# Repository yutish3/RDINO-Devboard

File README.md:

# Rdino - 2040
rp-2040 development board in the shape of arduino uno r3 so it supports its hats and also has esp32 for wifi and bluetooth and 5x5 grid of neo pixel leds

Journal 1	:- 2.0 hours

Journal 2	:- 1.5 hours

Journal 3	:- 0.4 hours

Journal 4	:- 1.5 hours

Journal 5	:- 1.0 hours

Journal 6	:- 1.5 hours

Journal 7	:- 1.3 hours

Journal 8	:- 2.0 hours

Journal 9	:- 1.0 hours

Journal 10	:- 0.5 hours

Journal 11	:- 2.0 hours

Journal 12	:- 2.5 hours

Journal 13	:- 2.0 hours

Journal 14	:- 5.2 hours

Journal 15	:- 1.0 hours

Journal 16	:- 0.5 hours

Journal 17	:- 0.5 hours

Journal 18	:- 5.5 hours

Journal 19	:- 2.0 hours

Journal 20	:- 3.0 hours

## VISION
main goals I had was making it is that I wanted to have a powerful board on which Arduino hats can fit with wireless capabilities so I used both rp 2040 and esp 32 and connected gpios of both so rp 2040 can off load some tasks to esp 32. so in a sense it is like Arduino UNO but on steroids 

and for usage too it can be used like a normal Arduino UNO 

it has dual microcontroller so all the less important repetative tasks can be off loaded to esp32 and main work can be done by the rp 2040 chip with extra 16M bit memory
and it can be used foor any project like lfr robot , micromouse , rc car etc

## what makes it special (main components)
&#9679; RP2040 :- main microcontroller

&#9679; W25Q128JVS :- 128Mbit Flash Memory for extra juice

&#9679; ESP32-C3-WROOM-02 :- backup microcontroller with wifi and Bluetooth capabilities 

&#9679; 25 X WS2812B-2020 :- programmable rgb leds

## Images

| Component | Purpose | Qty | Cost (INR) | Distributor |
| --- | --- | --- | --- | --- |
| RP2040 (QFN-56) | Main Microcontroller | 1 | ₹81.00 | [Evelta](https://evelta.com/rp2040-264kb-sram-dual-arm-cortex-m0-processor-mcu-by-raspberry-pi/?srsltid=AfmBOopaIG6fpnSNGs3z4S0e6P0bgP9_VYOyHm1yW1iu5uU8jt_uu5J_) |
| ESP32-C3-WROOM-02 | Wi-Fi / BLE Module | 1 | ₹312 | [Evelta](https://evelta.com/esp32-c3-wroom-02-n4-wi-fi-ble-module-4mb-flash-pcb-antenna/?sku=136-ESP32-C3-WROOM-02-N4&utm_source=google&utm_campaign=19958243666&utm_medium=cpc&utm_content=&utm_term=&gad_source=1&gad_campaignid=19958265965&gclid=Cj0KCQjwsMLSBhD9ARIsAIpUTDqEPgMN1OtKYFDDmMqUSGKSXAjHzA4DRwzgzZp3zSiW1o8-RgKeGbgaAoSMEALw_wcB) |
| W25Q128JVS (SOIC-8) | 128Mbit Flash Memory | 1 | ₹223 | [Evelta](https://evelta.com/serial-nor-flash-memory-128mbit-8pin-soic/?sku=153-W25Q128JVSIQ&utm_source=google&utm_campaign=19958243666&utm_medium=cpc&utm_content=&utm_term=&gad_source=1&gad_campaignid=19958265965&gclid=Cj0KCQjwsMLSBhD9ARIsAIpUTDqgAe2PFV_ZbwzCVTig-jSF6n-lNv5TzVO5kI0fkOoLNDz-UcC87KoaAvCyEALw_wcB) |
| AP2112K-3.3 (SOT-23-5) | 3.3V LDO Voltage Regulator | 1 | ₹24 | [Evelta](https://evelta.com/linear-voltage-regulator-positive-fixed-1-output-300ma-ic-sot-23-5/?sku=035-TLV74033PDBVR&utm_source=google&utm_campaign=19958243666&utm_medium=cpc&utm_content=&utm_term=&gad_source=1&gad_campaignid=19958265965&gclid=Cj0KCQjwsMLSBhD9ARIsAIpUTDpVNRkkdR8DkeeqQDI-B0SV4mmE5r7KHuDlczT8pWqQnIAxcDNvTTQaAnOdEALw_wcB#productDescription) |
| WS2812B-2020 (PLCC4) | Addressable RGB LEDs (D1-D24, D27, D29, D31) | 25 | ₹275 | [Robu](https://robu.in/product/1-month-warranty-953/?gad_source=1&gad_campaignid=17427802703&gclid=Cj0KCQjwsMLSBhD9ARIsAIpUTDpt1pzF430Rd8rggMbqOhyDVxqaDctheh1CFh1cCbUzKa_cTqI4nuYaAhGvEALw_wcB) |
| 74AHCT125 | 3.3v to 5v converter | 1 | ₹113 | [Lioncircuit](https://www.lioncircuits.com/parts/74AHCT125PW%2C118) |
| Standard LED (0603) | Status Indicator (D26) | 1 | ₹3.3 | [evelta](https://evelta.com/0603-orange-chip-led/?srsltid=AfmBOopJK48IT0WFYCzFETDcCPIIkiPRop17X2j5vajIVfQTBZ31vxPa) |
| USB-C Receptacle 14-Pin | Power and Data Interface (J1) | 1 | ₹8 | [Hubtronics](https://hubtronics.in/usb-type-c-16p-female-connector-surface-mount?srsltid=AfmBOordf7MpBH0Qx-t9NQyY5B-fdjtzOuCBNZ2MHx8Cz8tkCzKM3Jp4zG4) |
| 1x04 Pin Header/Socket | I/O Expansion / Programming (J6) | 1 | ₹11 | [Robu](https://robu.in/product/fh2-0-09-04pzd-xunpu-plugin1x4-pin-2mm-female-headers-rohs/?gad_source=1&gad_campaignid=17427802703&gclid=CjwKCAjw08fSBhA7EiwAfbQTsMGuGFKjKxeAs85tsGpJZ_VgBg9C0syUiuKSdEVnRGq6vaZT8pyhIhoCEKcQAvD_BwE)|
| 1x06 Pin Header/Socket | I/O Expansion (J2) | 5 | ₹53 | [Robu](https://robu.in/product/6-pin-female-11mm-tall-stackable-header-connector-for-arduino-5pcs/) |
| 1x08 Pin Header/Socket | I/O Expansion (J4, J5) | 2 | ₹32 | [Robu](https://robu.in/product/fh1-27-01-08pzd-xunpu-plugin1x8-pin-1-27mm-female-headers-rohs/?gad_source=1&gad_campaignid=17427802703&gclid=CjwKCAjw08fSBhA7EiwAfbQTsAXYrqE1Rld57TzQKy9yslqVRvfkEbmGVCeCCZim9T4gCUaC_6xX4xoCpCAQAvD_BwE) |
| 1x10 Pin Header/Socket | I/O Expansion (J3) | 1 | ₹17 | [Robu](https://robu.in/product/fh1-27-01-10pzd-xunpu-plugin1x10-pin-1-27mm-female-headers-rohs/) |
| Push Button (KMR2) | Reset / User Input (SW1, SW2) | 2 | ₹126 | [Robu](https://robu.in/product/kmr221nglfs-ck-2-8mm-0-5mm-round-button-50ma-vertical-welding-4-2mm-spst-2n-32v-smd-tactile-switches-rohs/) |
| 1.1kΩ Resistor (0603) | Current Limiting / Pull-up | 1 | ₹1 | [Robu](https://robu.in/product/0603waj0112t5e-uniohm-royal-ohm-100mw-thick-film-resistors-75v-%C2%B1100ppm-%E2%84%83%C2%B15-1-1k%CF%89-0603-chip-resistor-surface-mount-rohs/) |
| 4.7kΩ Resistor (0603) | I2C / General Pull-up | 2 | ₹5 | [Robu](https://robu.in/product/rt0603brd074k7l-yageo-res-thin-film-0603-4-7k-ohm-0-1-0-1w1-10w-%C2%B125ppm-c-pad-smd-t-r/) |
| 10kΩ Resistor (0603) | Pull-up / Pull-down | 3 | ₹3 | [Robu](https://robu.in/product/10k-ohm-1-4w-0603-surface-mount-chip-resistor-pack-of-100/) |
| 5.1kΩ Resistor (0603) | USB-C CC line Pull-down | 2 | ₹3 | [Robu](https://robu.in/product/rt0603fre075k1l-yageo-100mw-thin-film-resistor-75v-%C2%B150ppm-%E2%84%83-%C2%B11-5-1k%CF%89-0603-chip-resistor-surface-mount-rohs/) |
| 1μF Capacitor (0603) | Decoupling / Bypass | 6 | ₹8.5 | [Robu](https://robu.in/product/1uf-1000nf-50v-capacitor-0603-smd-package-pack-of-20/) |
| 10pF Capacitor (0603) | Crystal Load Capacitors | 2 | ₹1 | [Robu](https://robu.in/product/10pf-0603-surface-mount-multilayer-ceramic-capacitor-pack-of-50/) |
| Crystal 3225 (4-Pin) | Clock Source for RP2040 (Y1) | 1 | ₹101 | [lion circuit](https://www.lioncircuits.com/parts/NX3225SA-12MHZ-STD-CSR-6) |
| PCB | PCB | 1 | ₹3375 | [Robu] |
| Hot plate | soldering | 1 | ₹2,749 | [Amazon](https://www.amazon.in/Preheating-Soldering-Preheater-Platform-56x56x35mm/dp/B0C7W3W8C4?source=ps-sl-shoppingads-lpcontext&psc=1&smid=A2PRL1RFFZO5CK) |
| soldering flux | gooye paste to combine components | 1 | ₹400 | [amazon](https://www.amazon.in/Electron-Soldering-Syringe-No-Clean-Electronics/dp/B0GTMJHBJ4) |

The Bare Components : ₹1,708.80

PCB Fabrication (Robu): ₹3,375.00

Assembly Tools (Amazon): ₹3,262.00

Grand Total: ₹8,345.8

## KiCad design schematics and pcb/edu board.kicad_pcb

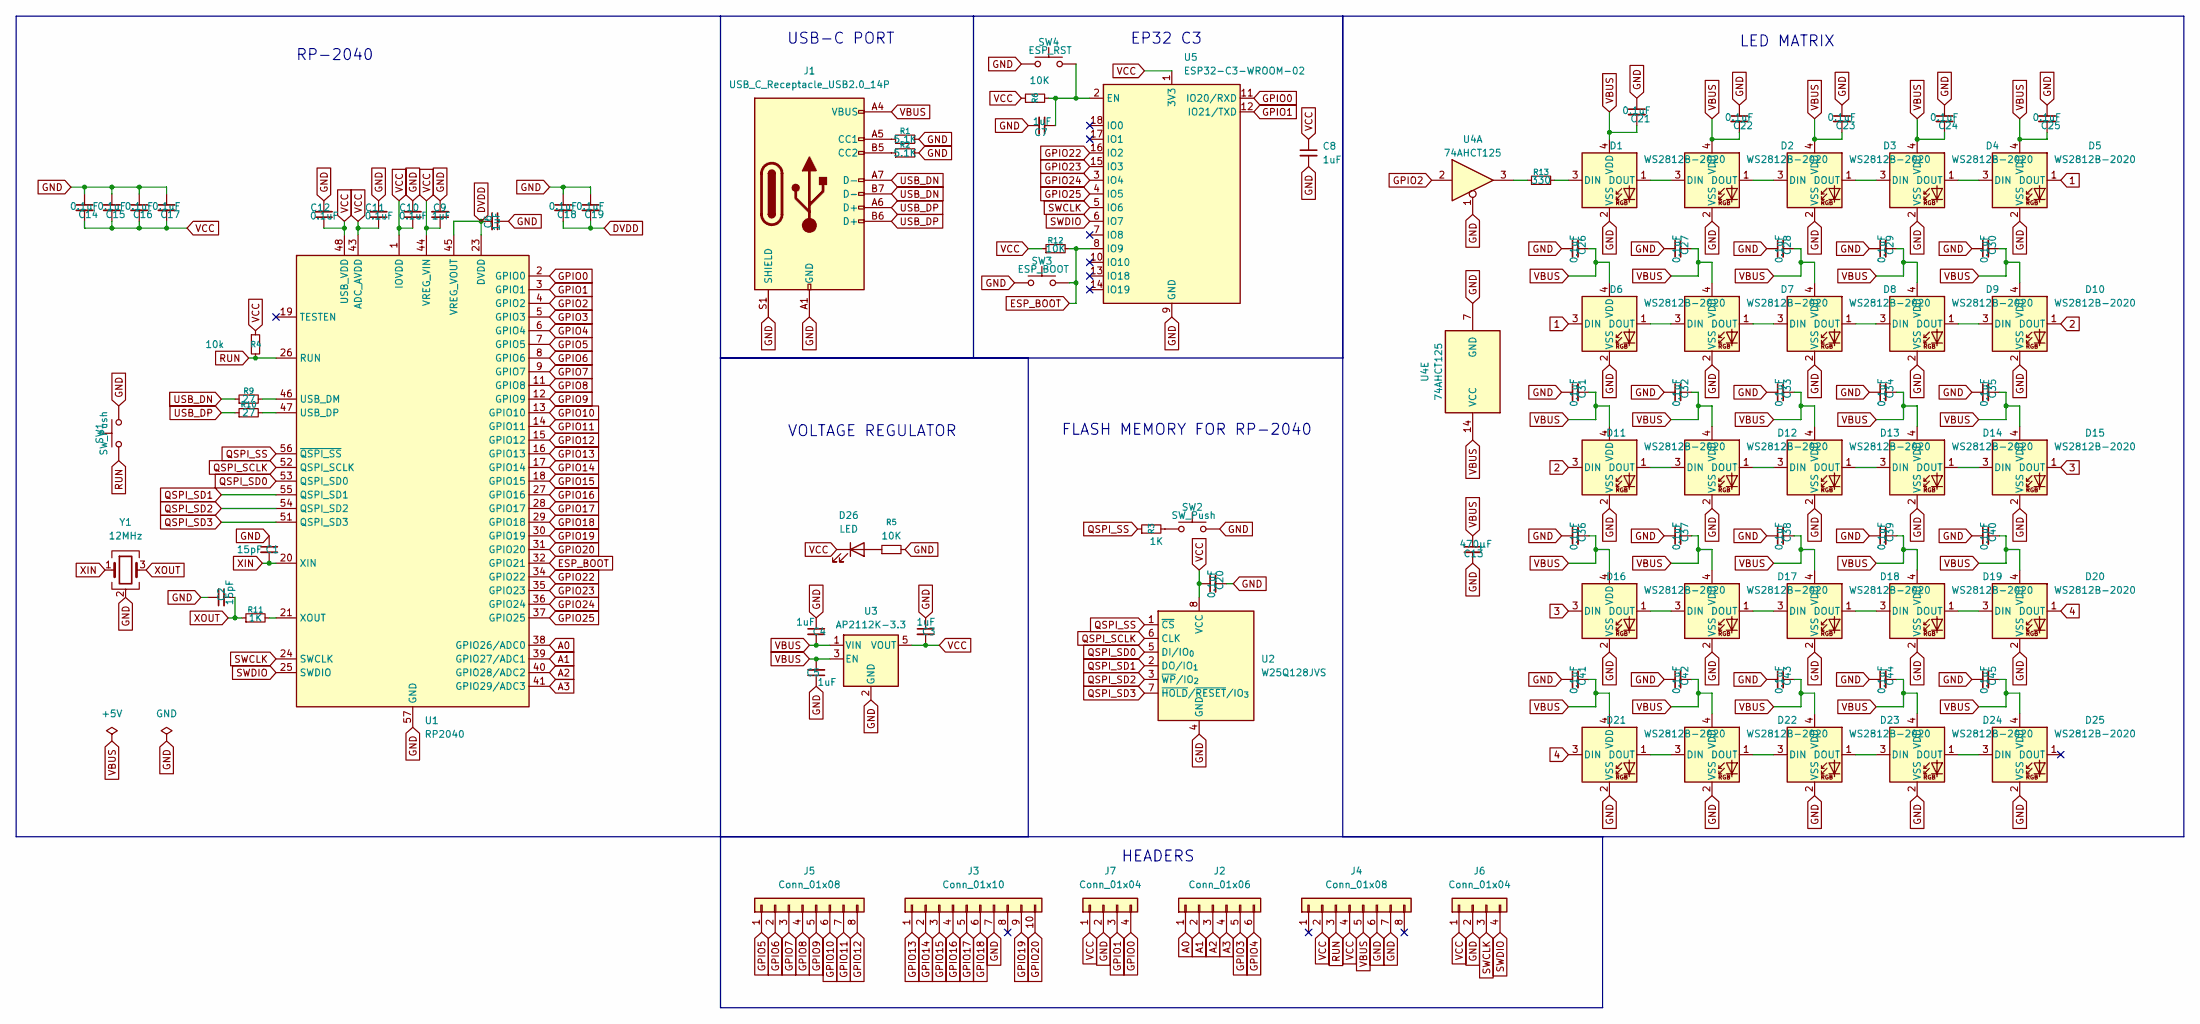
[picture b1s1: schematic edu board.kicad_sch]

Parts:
C1, C2: 15pF; C_0201_0603Metric
C3, C4, C5, C6, C7, C8, C9: 1uF; C_0201_0603Metric
C10, C11, C12, C14, C15, C16, C17, C18, C19, C20, C21, C22, C23, C24, C25, C26, C27, C28, C29, C30, C31, C32, C33, C34, C35, C36, C37, C38, C39, C40, C41, C42, C43, C44, C45: 0.1uF; C_0201_0603Metric
C13: 470μF; C_0201_0603Metric
D1, D2, D3, D4, D5, D6, D7, D8, D9, D10, D11, D12, D13, D14, D15, D16, D17, D18, D19, D20, D21, D22, D23, D24, D25: WS2812B-2020; LED_WS2812B-2020_PLCC4_2.0x2.0mm
D26: LED; LED_0603_1608Metric
J1: USB_C_Receptacle_USB2.0_14P; USB_C_Receptacle_HRO_TYPE-C-31-M-12
J2: Conn_01x06; PinSocket_1x06_P2.54mm_Vertical
J3: Conn_01x10; PinSocket_1x10_P2.54mm_Vertical
J4, J5: Conn_01x08; PinSocket_1x08_P2.54mm_Vertical
J6, J7: Conn_01x04; PinHeader_1x04_P2.54mm_Vertical
R1, R2: 5.1K; R_0201_0603Metric
R3, R11: 1K; R_0201_0603Metric
R4: 10k; R_0201_0603Metric
R5, R6, R12: 10K; R_0201_0603Metric
R9, R10: 27; R_0201_0603Metric
R13: 330; R_0201_0603Metric
SW1, SW2: SW_Push; SW_Push_1P1T_NO_CK_KMR2
SW3: ESP_BOOT; SW_Push_1P1T_NO_CK_KMR2
SW4: ESP_RST; SW_Push_1P1T_NO_CK_KMR2
U1: RP2040; QFN-56-1EP_7x7mm_P0.4mm_EP3.2x3.2mm
U2: W25Q128JVS; SOIC-8_5.3x5.3mm_P1.27mm
U3: AP2112K-3.3; SOT-23-5
U4: 74AHCT125; TSSOP-14_4.4x5mm_P0.65mm
U5: ESP32-C3-WROOM-02
Y1: 12MHz; Crystal_SMD_3225-4Pin_3.2x2.5mm

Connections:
1: D5.1 (DOUT), D6.3 (DIN)
2: D10.1 (DOUT), D11.3 (DIN)
3: D15.1 (DOUT), D16.3 (DIN)
4: D20.1 (DOUT), D21.3 (DIN)
A0: J2.1, U1.38 (GPIO26/ADC0)
A1: J2.2, U1.39 (GPIO27/ADC1)
A2: J2.3, U1.40 (GPIO28/ADC2)
A3: J2.4, U1.41 (GPIO29/ADC3)
DVDD: C6.2, C18.2, C19.2, U1.23 (DVDD), U1.45 (VREG_VOUT), U1.50 (DVDD)
ESP_BOOT: R12.2, SW3.2, U1.32 (GPIO21), U5.8 (IO9)
GND: C1.1, C2.1, C3.1, C4.1, C5.1, C6.1, C7.2, C8.2, C9.2, C10.2, C11.2, C12.2, C13.2, C14.1, C15.1, C16.1, C17.1, C18.1, C19.1, C20.2, C21.1, C22.1, C23.1, C24.1, C25.1, C26.1, C27.1, C28.1, C29.1, C30.1, C31.1, C32.1, C33.1, C34.1, C35.1, C36.1, C37.1, C38.1, C39.1, C40.1, C41.1, C42.1, C43.1, C44.1, C45.1, D1.2 (VSS), D2.2 (VSS), D3.2 (VSS), D4.2 (VSS), D5.2 (VSS), D6.2 (VSS), D7.2 (VSS), D8.2 (VSS), D9.2 (VSS), D10.2 (VSS), D11.2 (VSS), D12.2 (VSS), D13.2 (VSS), D14.2 (VSS), D15.2 (VSS), D16.2 (VSS), D17.2 (VSS), D18.2 (VSS), D19.2 (VSS), D20.2 (VSS), D21.2 (VSS), D22.2 (VSS), D23.2 (VSS), D24.2 (VSS), D25.2 (VSS), J1.A1 (GND), J1.A12 (GND), J1.B1 (GND), J1.B12 (GND), J1.S1 (SHIELD), J3.7, J4.6, J4.7, J6.2, J7.2, R1.2, R2.2, R5.2, SW1.2, SW2.2, SW3.1, SW4.1, U1.57 (GND), U2.4 (GND), U3.2 (GND), U4.1, U4.7 (GND), U5.9 (GND), U5.19 (GND), Y1.2 (G), Y1.4 (G)
GPIO0: J7.4, U1.2 (GPIO0), U5.11 (IO20/RXD)
GPIO1: J7.3, U1.3 (GPIO1), U5.12 (IO21/TXD)
GPIO2: U1.4 (GPIO2), U4.2
GPIO3: J2.5, U1.5 (GPIO3)
GPIO4: J2.6, U1.6 (GPIO4)
GPIO5: J5.1, U1.7 (GPIO5)
GPIO6: J5.2, U1.8 (GPIO6)
GPIO7: J5.3, U1.9 (GPIO7)
GPIO8: J5.4, U1.11 (GPIO8)
GPIO9: J5.5, U1.12 (GPIO9)
GPIO10: J5.6, U1.13 (GPIO10)
GPIO11: J5.7, U1.14 (GPIO11)
GPIO12: J5.8, U1.15 (GPIO12)
GPIO13: J3.1, U1.16 (GPIO13)
GPIO14: J3.2, U1.17 (GPIO14)
GPIO15: J3.3, U1.18 (GPIO15)
GPIO16: J3.4, U1.27 (GPIO16)
GPIO17: J3.5, U1.28 (GPIO17)
GPIO18: J3.6, U1.29 (GPIO18)
GPIO19: J3.9, U1.30 (GPIO19)
GPIO20: J3.10, U1.31 (GPIO20)
GPIO22: U1.34 (GPIO22), U5.16 (IO2)
GPIO23: U1.35 (GPIO23), U5.15 (IO3)
GPIO24: U1.36 (GPIO24), U5.3 (IO4)
GPIO25: U1.37 (GPIO25), U5.4 (IO5)
unnamed: D1.3 (DIN), R13.2
unnamed: D1.1 (DOUT), D2.3 (DIN)
unnamed: D2.1 (DOUT), D3.3 (DIN)
unnamed: D3.1 (DOUT), D4.3 (DIN)
unnamed: D4.1 (DOUT), D5.3 (DIN)
unnamed: D6.1 (DOUT), D7.3 (DIN)
unnamed: D7.1 (DOUT), D8.3 (DIN)
unnamed: D8.1 (DOUT), D9.3 (DIN)
unnamed: D9.1 (DOUT), D10.3 (DIN)
unnamed: D11.1 (DOUT), D12.3 (DIN)
unnamed: D12.1 (DOUT), D13.3 (DIN)
unnamed: D13.1 (DOUT), D14.3 (DIN)
unnamed: D14.1 (DOUT), D15.3 (DIN)
unnamed: D16.1 (DOUT), D17.3 (DIN)
unnamed: D17.1 (DOUT), D18.3 (DIN)
unnamed: D18.1 (DOUT), D19.3 (DIN)
unnamed: D19.1 (DOUT), D20.3 (DIN)
unnamed: D21.1 (DOUT), D22.3 (DIN)
unnamed: D22.1 (DOUT), D23.3 (DIN)
unnamed: D23.1 (DOUT), D24.3 (DIN)
unnamed: D24.1 (DOUT), D25.3 (DIN)
unnamed: D26.2 (A), R5.1
unnamed: J1.A5 (CC1), R1.1
unnamed: J1.B5 (CC2), R2.1
unnamed: R3.2, SW2.1
unnamed: R13.1, U4.3
unnamed: R9.2, U1.46 (USB_DM)
unnamed: R10.2, U1.47 (USB_DP)
unnamed: R11.2, U1.21 (XOUT)
unnamed: C7.1, R6.2, SW4.2, U5.2 (EN)
QSPI_SCLK: U1.52 (QSPI_SCLK), U2.6 (CLK)
QSPI_SD0: U1.53 (QSPI_SD0), U2.5 (DI/IO_{0})
QSPI_SD1: U1.55 (QSPI_SD1), U2.2 (DO/IO_{1})
QSPI_SD2: U1.54 (QSPI_SD2), U2.3 (~WP/IO_{2})
QSPI_SD3: U1.51 (QSPI_SD3), U2.7 (~HOLD/~RESET/IO_{3})
QSPI_SS: R3.1, U1.56 (~QSPI_SS), U2.1 (~CS)
RUN: J4.3, R4.2, SW1.1, U1.26 (RUN)
SWCLK: J6.3, U1.24 (SWCLK), U5.5 (IO6)
SWDIO: J6.4, U1.25 (SWDIO), U5.6 (IO7)
USB_DN: J1.A7 (D-), J1.B7 (D-), R9.1
USB_DP: J1.A6 (D+), J1.B6 (D+), R10.1
VBUS: C4.2, C5.2, C13.1, C21.2, C22.2, C23.2, C24.2, C25.2, C26.2, C27.2, C28.2, C29.2, C30.2, C31.2, C32.2, C33.2, C34.2, C35.2, C36.2, C37.2, C38.2, C39.2, C40.2, C41.2, C42.2, C43.2, C44.2, C45.2, D1.4 (VDD), D2.4 (VDD), D3.4 (VDD), D4.4 (VDD), D5.4 (VDD), D6.4 (VDD), D7.4 (VDD), D8.4 (VDD), D9.4 (VDD), D10.4 (VDD), D11.4 (VDD), D12.4 (VDD), D13.4 (VDD), D14.4 (VDD), D15.4 (VDD), D16.4 (VDD), D17.4 (VDD), D18.4 (VDD), D19.4 (VDD), D20.4 (VDD), D21.4 (VDD), D22.4 (VDD), D23.4 (VDD), D24.4 (VDD), D25.4 (VDD), J1.A4 (VBUS), J1.A9 (VBUS), J1.B4 (VBUS), J1.B9 (VBUS), J4.5, U3.1 (VIN), U3.3 (EN), U4.14 (VCC)
VCC: C3.2, C8.1, C9.1, C10.1, C11.1, C12.1, C14.2, C15.2, C16.2, C17.2, C20.1, D26.1 (K), J4.2, J4.4, J6.1, J7.1, R4.1, R6.1, R12.1, U1.1 (IOVDD), U1.10 (IOVDD), U1.22 (IOVDD), U1.33 (IOVDD), U1.42 (IOVDD), U1.43 (ADC_AVDD), U1.44 (VREG_VIN), U1.48 (USB_VDD), U1.49 (IOVDD), U2.8 (VCC), U3.5 (VOUT), U5.1 (3V3)
XIN: C1.2, U1.20 (XIN), Y1.1
XOUT: C2.2, R11.1, Y1.3

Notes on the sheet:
USB-C PORT
FLASH MEMORY FOR RP-2040
RP-2040
LED MATRIX
VOLTAGE REGULATOR
EP32 C3
HEADERS

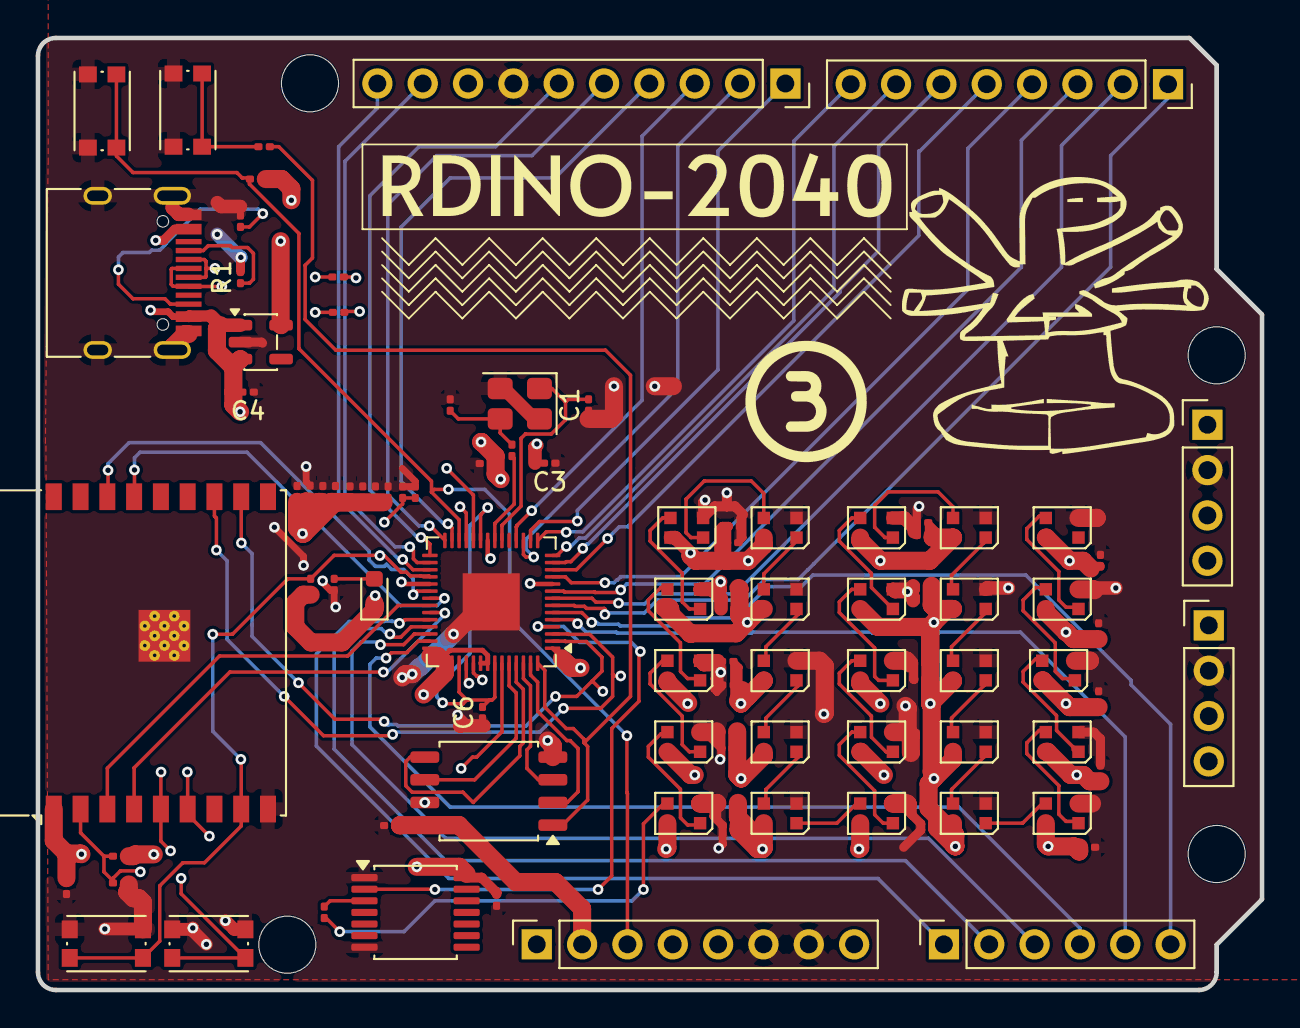
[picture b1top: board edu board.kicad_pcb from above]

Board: 4 copper layers, 68.6 x 53.3 mm, 99 parts (0 on the bottom side), 81 nets.

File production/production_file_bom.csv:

Designator,Footprint,Quantity,Value,LCSC Part #
"C1, C2",0201,2,15pF,
"C10, C11, C12, C14, C15, C16, C17, C18, C19, C20, C21, C22, C23, C24, C25, C26, C27, C28, C29, C30, C31, C32, C33, C34, C35, C36, C37, C38, C39, C40, C41, C42, C43, C44, C45",0201,35,0.1uF,
C13,0201,1,470μF,
"C3, C4, C5, C6, C7, C8, C9",0201,7,1uF,
"D1, D10, D11, D12, D13, D14, D15, D16, D17, D18, D19, D2, D20, D21, D22, D23, D24, D25, D3, D4, D5, D6, D7, D8, D9",LED_WS2812B-2020_PLCC4_2.0x2.0mm,25,WS2812B-2020,
D26,0603,1,LED,
J1,USB_C_Receptacle_HRO_TYPE-C-31-M-12,1,USB_C_Receptacle_USB2.0_14P,
J2,PinSocket_1x06_P2.54mm_Vertical,1,Conn_01x06,
J3,PinSocket_1x10_P2.54mm_Vertical,1,Conn_01x10,
"J4, J5",PinSocket_1x08_P2.54mm_Vertical,2,Conn_01x08,
"J6, J7",PinHeader_1x04_P2.54mm_Vertical,2,Conn_01x04,
"R1, R2",0201,2,5.1K,
"R10, R9",0201,2,27,
"R11, R3",0201,2,1K,
"R12, R4, R5, R6",0201,4,10K,
R13,0201,1,330,
"SW1, SW2",SW_Push_1P1T_NO_CK_KMR2,2,SW_Push,
SW3,SW_Push_1P1T_NO_CK_KMR2,1,ESP_BOOT,
SW4,SW_Push_1P1T_NO_CK_KMR2,1,ESP_RST,
U1,QFN-56-1EP_7x7mm_P0.4mm_EP3.2x3.2mm,1,RP2040,
U2,SOIC-8_5.3x5.3mm_P1.27mm,1,W25Q128JVS,
U3,SOT-23-5,1,AP2112K-3.3,
U4,TSSOP-14_4.4x5mm_P0.65mm,1,74AHCT125,
U5,ESP32-C3-WROOM-02,1,ESP32-C3-WROOM-02,
Y1,Crystal_SMD_3225-4Pin_3.2x2.5mm,1,12MHz,
